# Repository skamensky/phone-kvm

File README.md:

# phone-kvm

Gives an agent a real Android phone to use the way a person does. A small ESP32-S3 board
plugs into the phone's USB port as a keyboard, touchscreen and mouse, is powered by the phone,
and looks at the phone's screen with its own camera. Nothing is installed on the phone: no
app, no developer mode, no adb. Because the view is a camera, it works on any Android phone
and on every screen, lock screens included. Design: [docs/design.md](docs/design.md).

| Part | Where |
| --- | --- |
| Firmware (ESP-IDF, C) | `firmware/` |
| The board (KiCad, generated from `hardware/circuit.py`) | `hardware/`, `tools/` |
| The simulated board (devices added to Espressif's QEMU) | `sim/qemu/` |
| Host software: `phonectl` | `phone_kvm/` |
| The virtual rig around the simulated board, and the tests | `rig/`, `tests/` |

The board has not been manufactured yet. The same firmware runs here on a simulated ESP32-S3
whose USB port is plugged into a virtual phone (the Android emulator) and whose camera looks
at that phone's screen.

## Virtual rig

Needs Linux with KVM, passwordless `sudo`, Nix, the stock kernel module `vhci-hcd` and
`usbip` (Ubuntu: `linux-tools-generic`). The flake accepts the Android SDK licence.

    bin/rig up        # builds the firmware, boots the board, plugs it into the phone;
                      # about a minute; prints status with "ready": true
    bin/rig status
    bin/rig down
    bin/check         # host logic, and everything end to end when the rig is up (3 minutes)

After `rig up`, find the screen and measure the pointer once:

    bin/phonectl key meta+i && bin/phonectl calibrate screen    # a light screen: Settings
    bin/phonectl key home && bin/phonectl calibrate pointer

### A real phone in the rig

The simulated board can drive a real phone that has USB debugging on, over USB or Wi-Fi, with
a webcam on this host as the board's camera:

    bin/rig up --phone real --serial 10.0.0.5:5555 --webcam /dev/video0 --rotate 0

`--serial` is the phone as `adb devices` names it. The phone gets the board's four HID
interfaces as devices in its own kernel (`rig/uhid.py`). `python -m rig.view` serves the
camera's picture to a browser, for aiming the webcam; `--rotate 90` turns it upright there.

The rig leaves the webcam's own settings alone. A phone's screen is lit in pulses, which a
webcam on automatic exposure shows as dark bands, and its picture is soft by default. On a
NexiGo N60 (fixed focus: the phone has to lie at the distance where it is sharp) this gave a
steady, sharp picture, and has to be given again after the webcam is replugged:

    v4l2-ctl -d /dev/video0 -c auto_exposure=1 -c exposure_time_absolute=166 -c gain=0 -c sharpness=200

## Using the phone

Every command prints one JSON object. Positions are pixels of the screenshot.

    bin/phonectl screenshot shot.png        # never older than the last input; waits for the
                                            # screen to settle (--settle-ms 0 to not)
    bin/phonectl tap 243 990                # --hold-ms 800 for a long press
    bin/phonectl swipe 243 800 243 300      # more points trace a path: an unlock pattern
    bin/phonectl pinch 243 500 --start 80 --end 300
    bin/phonectl type 'Hello, World!'
    bin/phonectl key enter                  # home back recents power volume-up ... ctrl+a meta+n
    bin/phonectl mouse to 187 715           # also: move DX DY, click [right], scroll N
    bin/phonectl calibrate                  # after setup, and after the phone or camera moves
    bin/phonectl frame raw.png              # the camera's whole frame, for aiming it
    bin/phonectl status

The loop for an agent is: `screenshot`, read the image, act, `screenshot`.

`mouse to` looks where the cursor landed and corrects it, so it takes a few seconds and answers
with `pointer` and `seen` (false when the cursor could not be found on the screen).

`screenshot` also reports `captured_at`, `ms_since_input`, `settled` and `pointer`: where the
mouse cursor is in that image, or null when it is not known. `calibrate` measures what ties
the image to the inputs: where the screen is in the camera's frame, how far the cursor moves
per mouse count, how long an input takes to show, and the camera's noise. `calibrate screen`
and `calibrate pointer` do the halves separately. The screen is found as a lit quadrilateral,
so `calibrate screen` needs a light screen that reaches all four edges; `calibrate pointer`
needs a screen that does not react to hovering (the home screen away from icons).

Unlocking: `key power` wakes the phone, a swipe up opens the entry screen, then `type` the
PIN or password and `key enter`, or `swipe` through the pattern's dots.

`bin/*` run inside the project's Nix shell; set `PHONE_KVM_SHELL=1` when already in it
(`nix develop`) to skip the start-up cost.

## The board

    nix develop .#board --command python3 tools/generate.py   # hardware/circuit.py -> schematic and PCB, routed
    nix develop .#board --command python3 tools/board.py      # ERC, DRC, order files, pictures

`tools/board.py` writes the JLCPCB order files to `build/fab/` and pictures of the board to
`build/board/`. The board is 32 x 50 mm, two layers, about $7 of parts. Edit the circuit in `hardware/circuit.py`, never the KiCad files.

## On the real board

    nix develop .#firmware --command firmware/build.sh board
    nix develop .#firmware --command idf.py -C firmware -B firmware/build-board -p /dev/ttyUSB0 flash monitor

The USB-C port belongs to the phone, so flashing and the console use the UART header with a
3.3 V USB serial adapter (hold BOOT, press RESET to enter the bootloader). On the console:

    wifi <network name> <password>
    token <16 or more characters>
    status

Then, from the computer the agent runs on, with the token in the environment (never in a file):

    export PHONE_KVM_TOKEN=...
    bin/phonectl setup --device <the board's address> --rotate 90
    bin/phonectl frame raw.png      # aim the camera, then calibrate as above

`--rotate` is how far clockwise the phone appears turned in the camera's frame. The phone's
screen should fill most of the frame, on a dark surface, without glare.

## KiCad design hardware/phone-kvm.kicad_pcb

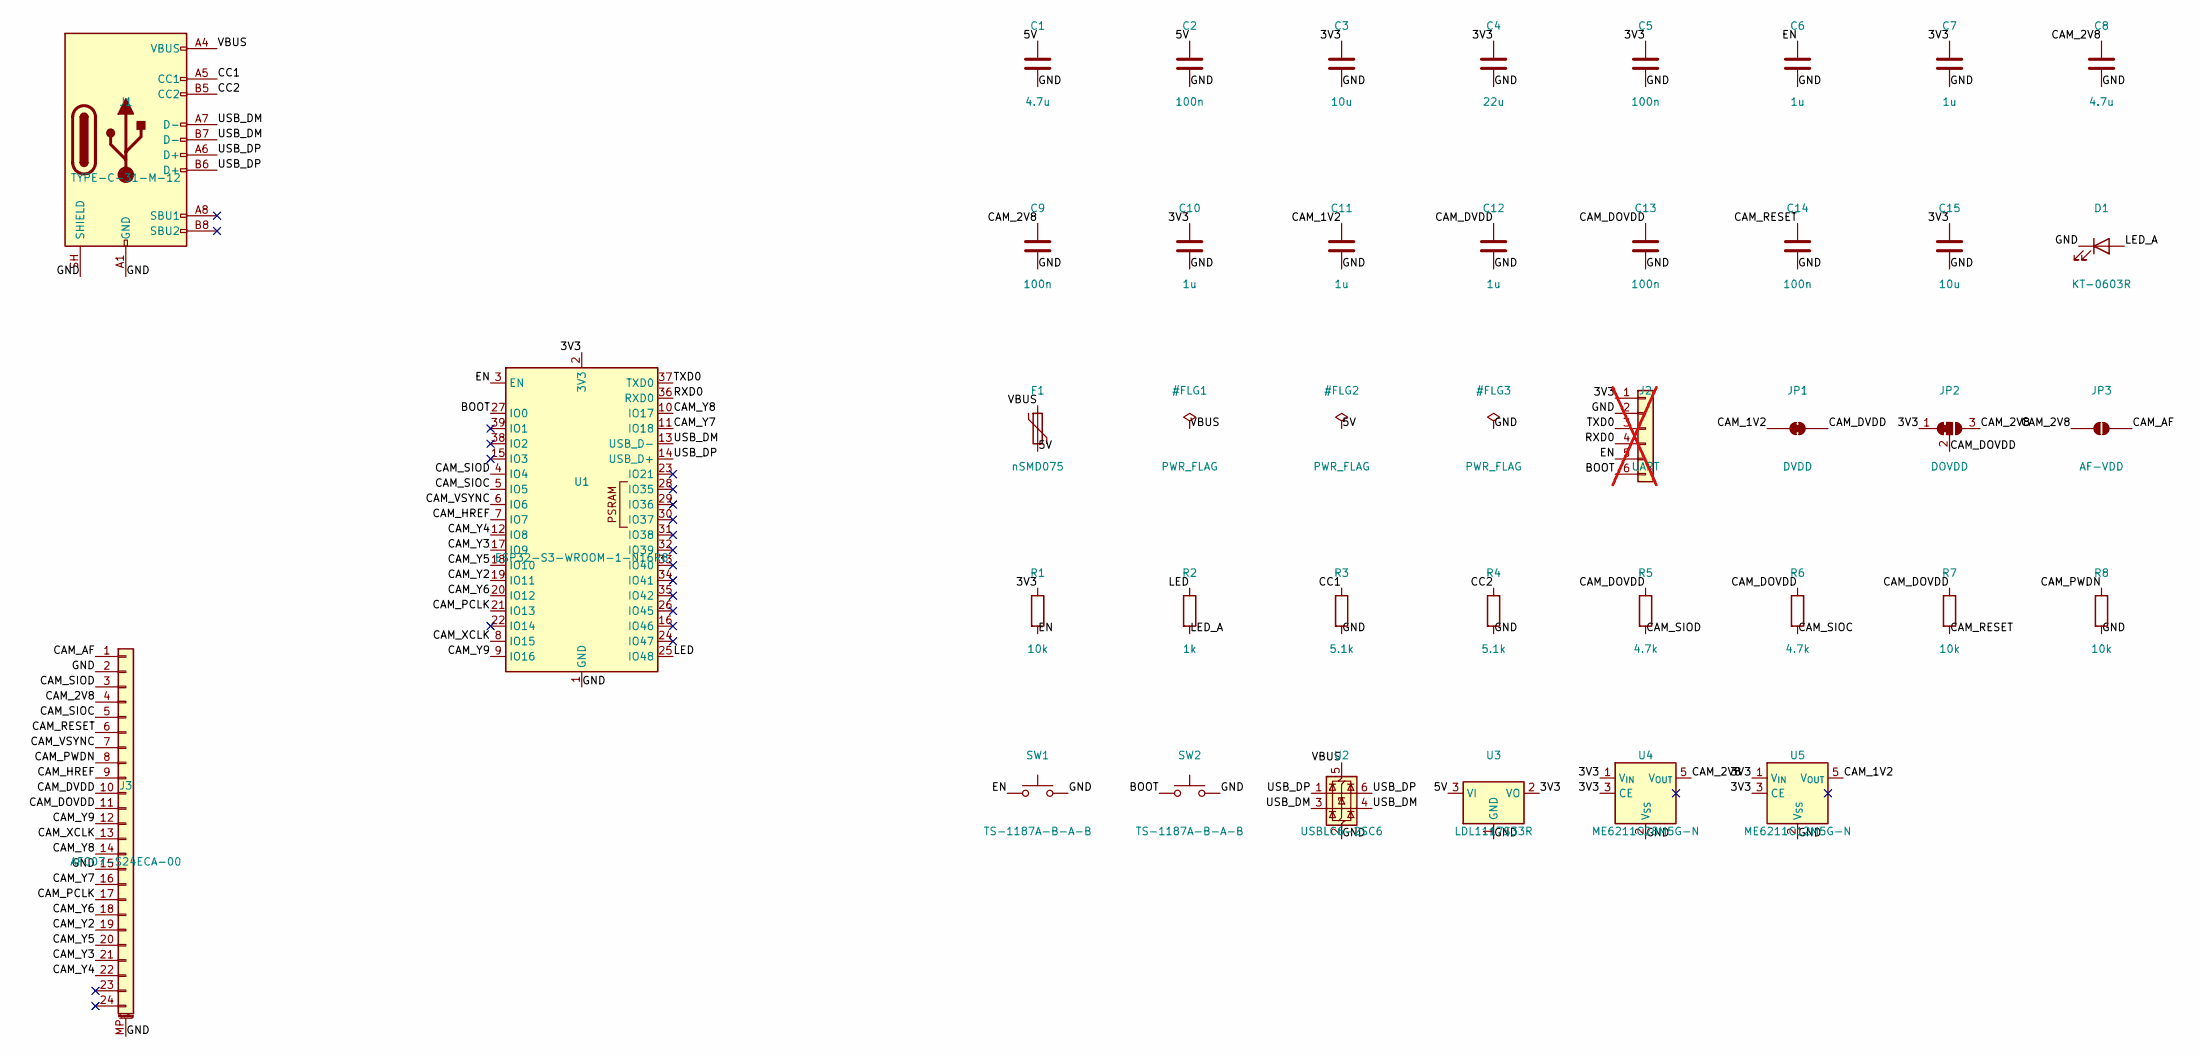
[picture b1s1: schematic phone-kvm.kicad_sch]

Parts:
C1, C8: 4.7u; C_0603_1608Metric; LCSC C19666
C2, C5, C9, C13, C14: 100n; C_0603_1608Metric; LCSC C14663
C3, C15: 10u; C_0603_1608Metric; LCSC C19702
C4: 22u; C_0805_2012Metric; LCSC C45783
C6, C7, C10, C11, C12: 1u; C_0603_1608Metric; LCSC C15849
D1: KT-0603R; LED_0603_1608Metric; LCSC C2286
F1: nSMD075; Fuse_1206_3216Metric; LCSC C70078
J1: TYPE-C-31-M-12; USB_C_Receptacle_HRO_TYPE-C-31-M-12; LCSC C165948
J2: UART; PinHeader_1x06_P2.54mm_Vertical; not fitted
J3: AFC07-S24ECA-00; Jushuo_AFC07-S24FCA-00_1x24-1MP_P0.50_Horizontal; LCSC C262643
JP1: DVDD; SolderJumper-2_P1.3mm_Bridged_RoundedPad1.0x1.5mm
JP2: DOVDD; SolderJumper-3_P1.3mm_Bridged12_RoundedPad1.0x1.5mm
JP3: AF-VDD; SolderJumper-2_P1.3mm_Open_RoundedPad1.0x1.5mm
R1, R7, R8: 10k; R_0603_1608Metric; LCSC C25804
R2: 1k; R_0603_1608Metric; LCSC C21190
R3, R4: 5.1k; R_0603_1608Metric; LCSC C23186
R5, R6: 4.7k; R_0603_1608Metric; LCSC C23162
SW1, SW2: TS-1187A-B-A-B; SW_Push_1P1T_XKB_TS-1187A; LCSC C318884
U1: ESP32-S3-WROOM-1-N16R8; ESP32-S3-WROOM-1; LCSC C2913202
U2: USBLC6-2SC6; SOT-23-6; LCSC C7519
U3: LDL1117S33R; SOT-223-3_TabPin2; LCSC C435835
U4: ME6211C28M5G-N; SOT-23-5; LCSC C53099
U5: ME6211C12M5G-N; SOT-23-5; LCSC C236672

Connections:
/3V3: C3.1, C4.1, C5.1, C7.1, C10.1, C15.1, J2.1, JP2.1 (A), R1.1, U1.2 (3V3), U3.2 (VO), U4.1 (V_{IN}), U4.3 (CE), U5.1 (V_{IN}), U5.3 (CE)
/5V: C1.1, C2.1, F1.2, U3.3 (VI)
/BOOT: J2.6, SW2.1, U1.27 (IO0)
/CAM_1V2: C11.1, JP1.1 (A), U5.5 (V_{OUT})
/CAM_2V8: C8.1, C9.1, J3.4, JP2.3 (B), JP3.1 (A), U4.5 (V_{OUT})
/CAM_AF: J3.1, JP3.2 (B)
/CAM_DOVDD: C13.1, J3.11, JP2.2 (C), R5.1, R6.1, R7.1
/CAM_DVDD: C12.1, J3.10, JP1.2 (B)
/CAM_HREF: J3.9, U1.7 (IO7)
/CAM_PCLK: J3.17, U1.21 (IO13)
/CAM_PWDN: J3.8, R8.1
/CAM_RESET: C14.1, J3.6, R7.2
/CAM_SIOC: J3.5, R6.2, U1.5 (IO5)
/CAM_SIOD: J3.3, R5.2, U1.4 (IO4)
/CAM_VSYNC: J3.7, U1.6 (IO6)
/CAM_XCLK: J3.13, U1.8 (IO15)
/CAM_Y2: J3.19, U1.19 (IO11)
/CAM_Y3: J3.21, U1.17 (IO9)
/CAM_Y4: J3.22, U1.12 (IO8)
/CAM_Y5: J3.20, U1.18 (IO10)
/CAM_Y6: J3.18, U1.20 (IO12)
/CAM_Y7: J3.16, U1.11 (IO18)
/CAM_Y8: J3.14, U1.10 (IO17)
/CAM_Y9: J3.12, U1.9 (IO16)
/CC1: J1.A5 (CC1), R3.1
/CC2: J1.B5 (CC2), R4.1
/EN: C6.1, J2.5, R1.2, SW1.1, U1.3 (EN)
/GND: C1.2, C2.2, C3.2, C4.2, C5.2, C6.2, C7.2, C8.2, C9.2, C10.2, C11.2, C12.2, C13.2, C14.2, C15.2, D1.1 (K), J1.A1 (GND), J1.A12 (GND), J1.B1 (GND), J1.B12 (GND), J1.SH (SHIELD), J2.2, J3.2, J3.15, J3.MP (MountPin), R3.2, R4.2, R8.2, SW1.2, SW2.2, U1.1 (GND), U1.40 (GND), U1.41 (GND), U2.2 (GND), U3.1 (GND), U4.2 (V_{SS}), U5.2 (V_{SS})
/LED: R2.1, U1.25 (IO48)
/LED_A: D1.2 (A), R2.2
/RXD0: J2.4, U1.36 (RXD0)
/TXD0: J2.3, U1.37 (TXD0)
/USB_DM: J1.A7 (D-), J1.B7 (D-), U1.13 (USB_D-), U2.3 (I/O2), U2.4 (I/O2)
/USB_DP: J1.A6 (D+), J1.B6 (D+), U1.14 (USB_D+), U2.1 (I/O1), U2.6 (I/O1)
/VBUS: F1.1, J1.A4 (VBUS), J1.A9 (VBUS), J1.B4 (VBUS), J1.B9 (VBUS), U2.5 (VBUS)

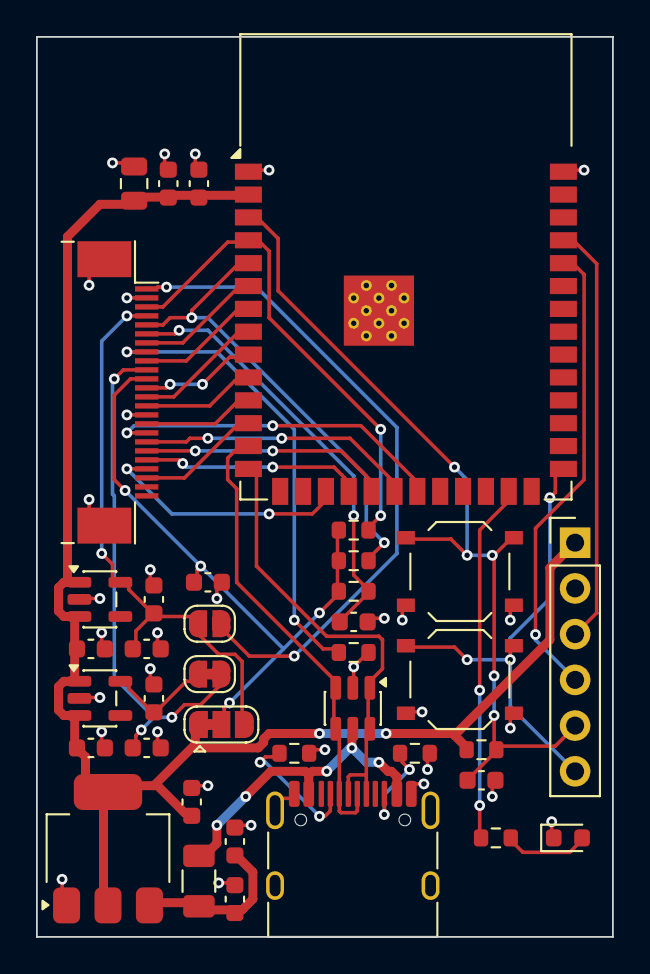
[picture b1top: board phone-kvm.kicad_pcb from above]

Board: 2 copper layers, 32.0 x 50.0 mm, 38 parts (0 on the bottom side), 35 nets.
